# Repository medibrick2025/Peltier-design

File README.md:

# Peltier Brick Controller

## Description

The Peltier Brick is a modular controller designed to operate two independent Peltier heating and cooling modules. Each channel uses an IR2113 gate driver together with IRF3205 MOSFETs to form a switching stage that allows bidirectional current flow. By reversing the current through the Peltier device, the system can provide both heating and cooling.

A microcontroller generates PWM signals to regulate the power delivered to each Peltier element and control the temperature of each channel independently.

---

## PCB Layout

The images below show the front and back sides of the PCB design.

## Schematics

The image below shows the circuit schematic for the PCB.

---

## Electrical Hardware

KiCad PCB design files and manufacturing outputs:

[Electrical Hardware](Electrical_Hardware/)

---

## GUI

The project also includes a graphical user interface (GUI) for system control and monitoring.

The GUI supports basic interaction with the Peltier system, including control input and display of system status.

[GUI](GUI/)

---

## Datasheets and Design Notes

Power driver discussion and reference documentation:

[DataSheet](DataSheet/)

---

## Assembly and instructions

These are the [Assebly and Instructions](Assembly_and_instructions/)

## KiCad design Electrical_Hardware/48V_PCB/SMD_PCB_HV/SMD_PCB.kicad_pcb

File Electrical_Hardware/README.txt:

# PCB Ordering Guide

This folder contains the PCB manufacturing files for the Peltier hardware system.  

## PCB File Locations

```text
Electrical_Hardware/12V_PCB/SMD_PCB/
Electrical_Hardware/48V_PCB/SMD_PCB_HV/
Electrical_Hardware/Faceplate_PCB/
```

## How to Order the PCB

1. Download this repository from GitHub by clicking **Code → Download ZIP**, or clone it with Git.  

2. Open the `Electrical_Hardware` folder and choose the PCB folder you want to order.  

3. Compress the selected PCB folder into a `.zip` file.  

```text
12V_PCB/SMD_PCB/       →  SMD_PCB.zip
48V_PCB/SMD_PCB_HV/    →  SMD_PCB_HV.zip
Faceplate_PCB/         →  Faceplate_PCB.zip
```

4. Upload the `.zip` file to PCBWay as the Gerber file package.  

5. Check the PCB preview, confirm the order settings, and submit the order.  

PCBWay will review the files before manufacturing.

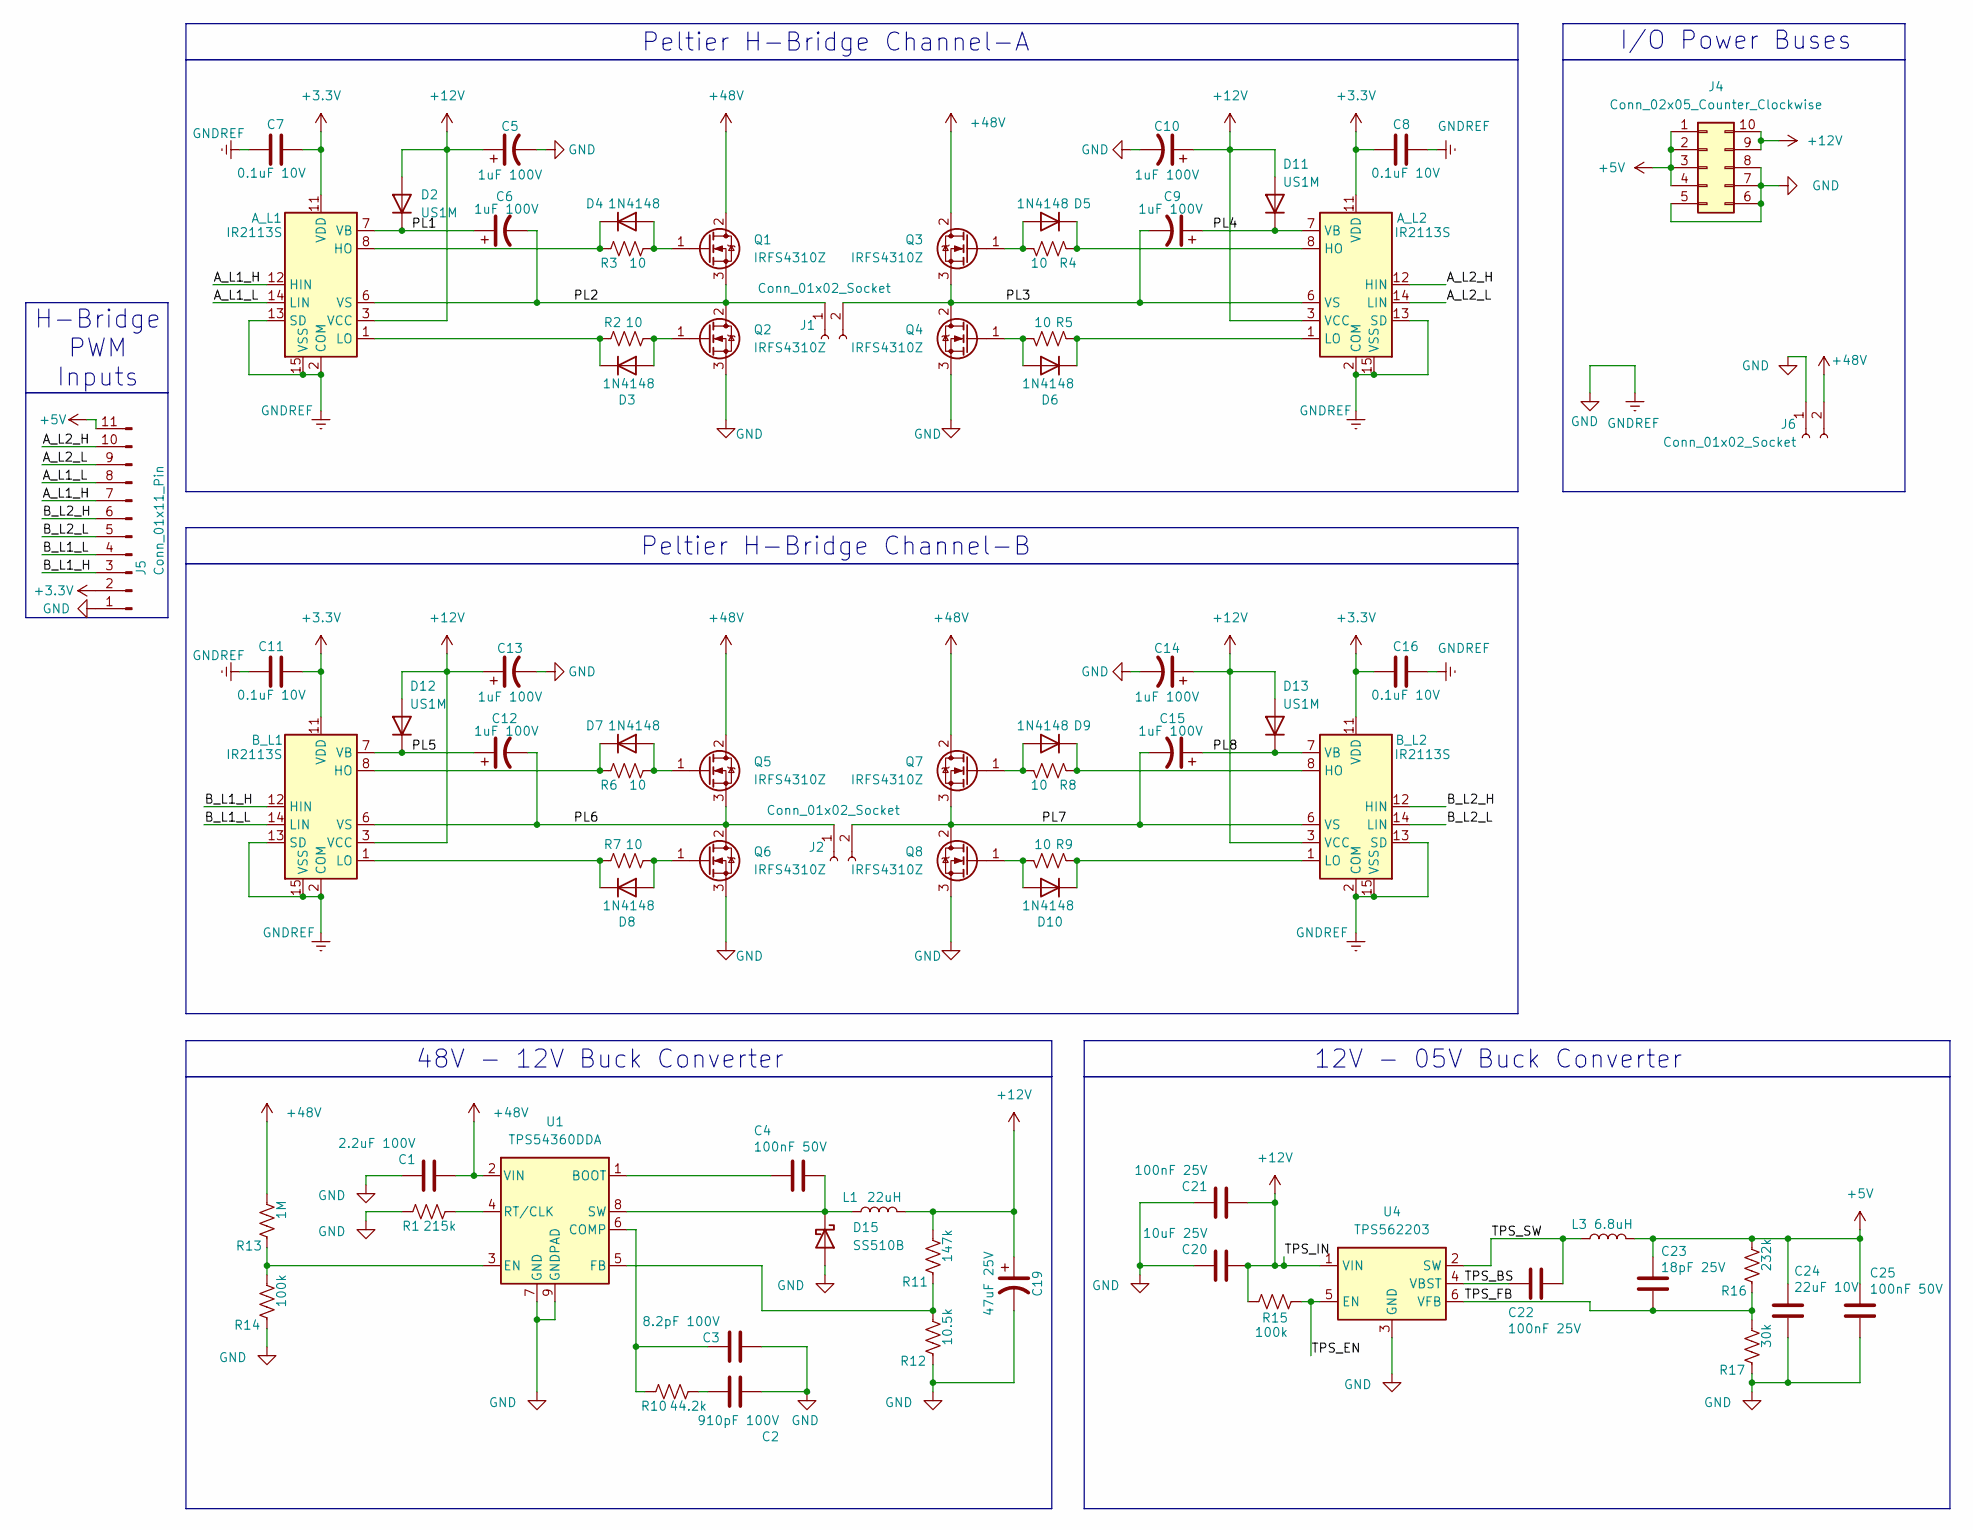
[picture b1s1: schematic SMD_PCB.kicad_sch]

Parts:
A_L1, A_L2: IR2113S; SOIC-16W_7.5x10.3mm_P1.27mm
B_L1, B_L2: IR2113S; SOIC-16W_7.5x10.3mm_P1.27mm
C1: 2.2uF 100V; C_1210_3225Metric
C2: 910pF 100V; C_0805_2012Metric
C3: 8.2pF 100V; C_0805_2012Metric
C4, C25: 100nF 50V; C_0603_1608Metric
C5, C6, C9, C10, C12, C13, C14, C15: 1uF 100V; C_1206_3216Metric
C7, C8, C11, C16: 0.1uF 10V; C_1206_3216Metric
C19: 47uF 25V; C_1206_3216Metric
C20: 10uF 25V; C_0805_2012Metric
C21, C22: 100nF 25V; C_0603_1608Metric
C23: 18pF 25V; C_0201_0603Metric
C24: 22uF 10V; C_0805_2012Metric
D2, D11, D12, D13: US1M; D_SMA
D3, D4, D5, D6, D7, D8, D9, D10: 1N4148; D_SOD-123
D15: SS510B; D_SMB
J1, J2, J6: Conn_01x02_Socket; AMASS_XT30PW-F_1x02_P2.50mm_Horizontal
J4: Conn_02x05_Counter_Clockwise; JST_PHD_B10B-PHDSS_2x05_P2.00mm_Vertical
J5: Conn_01x11_Pin; PinHeader_1x11_P2.54mm_Vertical
L1: 22uH; L_Bourns_SRR1260
L3: 6.8uH; L_Changjiang_FTC404030S
Q1, Q2, Q3, Q4, Q5, Q6, Q7, Q8: IRFS4310Z; TO-263-2
R1: 215k; R_0805_2012Metric
R2, R3, R4, R5, R6, R7, R8, R9: 10; R_1206_3216Metric
R10: 44.2k; R_0805_2012Metric
R11: 147k; R_0805_2012Metric
R12: 10.5k; R_0805_2012Metric
R13: 1M; R_0805_2012Metric
R14, R15: 100k; R_0805_2012Metric
R16: 232k; R_0805_2012Metric
R17: 30k; R_0805_2012Metric
U1: TPS54360DDA; TI_SO-PowerPAD-8_ThermalVias
U4: TPS562203; SOT-563

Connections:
+3.3V: A_L1.11 (VDD), A_L2.11 (VDD), B_L1.11 (VDD), B_L2.11 (VDD), C7.2, C8.2, C11.2, C16.2, J5.2
+5V: C23.2, C24.2, C25.2, J4.1, J4.2, J4.3, J4.4, J5.11, L3.2, R16.2
+12V: A_L1.3 (VCC), A_L2.3 (VCC), B_L1.3 (VCC), B_L2.3 (VCC), C5.1, C10.1, C13.1, C14.1, C19.1, C20.2, C21.2, D2.2 (A), D11.2 (A), D12.2 (A), D13.2 (A), J4.9, J4.10, L1.2, R11.2, R15.1, U4.1 (VIN)
+48V: C1.2, J6.2, Q1.2 (D), Q3.2 (D), Q5.2 (D), Q7.2 (D), R13.2, U1.2 (VIN)
/A_L1_H: A_L1.12 (HIN), J5.7
/A_L1_L: A_L1.14 (LIN), J5.8
/A_L2_H: A_L2.12 (HIN), J5.10
/A_L2_L: A_L2.14 (LIN), J5.9
/B_L1_H: B_L1.12 (HIN), J5.3
/B_L1_L: B_L1.14 (LIN), J5.4
/B_L2_H: B_L2.12 (HIN), J5.6
/B_L2_L: B_L2.14 (LIN), J5.5
/PL1: A_L1.7 (VB), C6.1, D2.1 (K)
/PL2: A_L1.6 (VS), C6.2, J1.1, Q1.3 (S), Q2.2 (D)
/PL3: A_L2.6 (VS), C9.2, J1.2, Q3.3 (S), Q4.2 (D)
/PL4: A_L2.7 (VB), C9.1, D11.1 (K)
/PL5: B_L1.7 (VB), C12.1, D12.1 (K)
/PL6: B_L1.6 (VS), C12.2, J2.1, Q5.3 (S), Q6.2 (D)
/PL7: B_L2.6 (VS), C15.2, J2.2, Q7.3 (S), Q8.2 (D)
/PL8: B_L2.7 (VB), C15.1, D13.1 (K)
/TPS_BS: C22.2, U4.4 (VBST)
/TPS_EN: R15.2, U4.5 (EN)
/TPS_FB: C23.1, R16.1, R17.2, U4.6 (VFB)
/TPS_SW: C22.1, L3.1, U4.2 (SW)
GND: A_L1.2 (COM), A_L1.13 (SD), A_L1.15 (VSS), A_L2.2 (COM), A_L2.13 (SD), A_L2.15 (VSS), B_L1.2 (COM), B_L1.13 (SD), B_L1.15 (VSS), B_L2.2 (COM), B_L2.13 (SD), B_L2.15 (VSS), C1.1, C2.2, C3.2, C5.2, C7.1, C8.1, C10.2, C11.1, C13.2, C14.2, C16.1, C19.2, C20.1, C21.1, C24.1, C25.1, D15.2 (A), J4.5, J4.6, J4.7, J4.8, J5.1, J6.1, Q2.3 (S), Q4.3 (S), Q6.3 (S), Q8.3 (S), R1.1, R12.1, R14.1, R17.1, U1.7 (GND), U1.9 (GNDPAD), U4.3 (GND)
unnamed: A_L1.8 (HO), D4.1 (K), R3.1
unnamed: A_L1.1 (LO), D3.1 (K), R2.1
unnamed: A_L2.8 (HO), D5.1 (K), R4.1
unnamed: A_L2.1 (LO), D6.1 (K), R5.1
unnamed: B_L1.8 (HO), D7.1 (K), R6.1
unnamed: B_L1.1 (LO), D8.1 (K), R7.1
unnamed: B_L2.8 (HO), D9.1 (K), R8.1
unnamed: B_L2.1 (LO), D10.1 (K), R9.1
unnamed: C2.1, R10.2
unnamed: D3.2 (A), Q2.1 (G), R2.2
unnamed: D4.2 (A), Q1.1 (G), R3.2
unnamed: D5.2 (A), Q3.1 (G), R4.2
unnamed: D6.2 (A), Q4.1 (G), R5.2
unnamed: D7.2 (A), Q5.1 (G), R6.2
unnamed: D8.2 (A), Q6.1 (G), R7.2
unnamed: D9.2 (A), Q7.1 (G), R8.2
unnamed: D10.2 (A), Q8.1 (G), R9.2
unnamed: C4.1, D15.1 (K), L1.1, U1.8 (SW)
unnamed: C4.2, U1.1 (BOOT)
unnamed: C3.1, R10.1, U1.6 (COMP)
unnamed: R13.1, R14.2, U1.3 (EN)
unnamed: R11.1, R12.2, U1.5 (FB)
unnamed: R1.2, U1.4 (RT/CLK)

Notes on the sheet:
I/O Power Buses
H-Bridge PWM Inputs
12V - 05V Buck Converter
Peltier H-Bridge Channel-A
Peltier H-Bridge Channel-B
48V - 12V Buck Converter

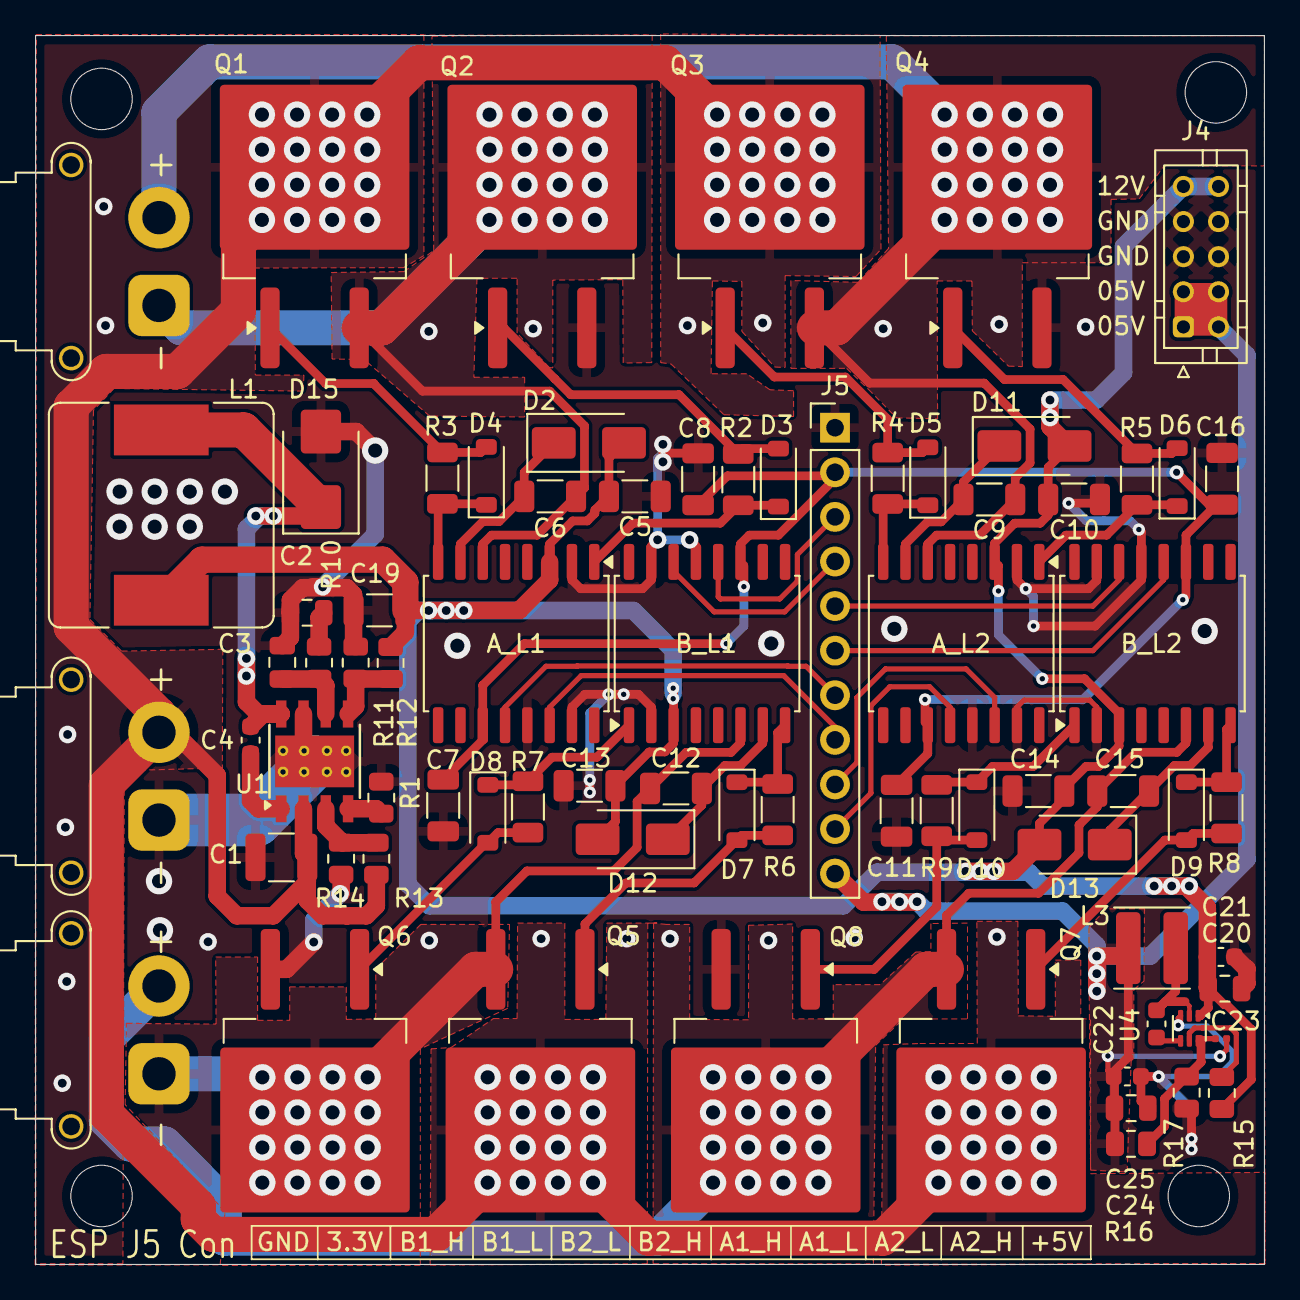
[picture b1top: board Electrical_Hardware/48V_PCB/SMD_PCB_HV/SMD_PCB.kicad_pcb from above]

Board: 2 copper layers, 70.0 x 70.0 mm, 74 parts (0 on the bottom side), 48 nets.

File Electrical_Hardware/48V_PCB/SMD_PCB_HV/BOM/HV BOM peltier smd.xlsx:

Item # | Designator | Qty | Manufacturer | Mfg Part # | LCSC Part# | Description / Value | Packaging | Type | Cost | Footprint | Remark
1 | Q1,Q2,Q3,Q4,Q5,Q6,Q7,Q8 | 8 | HXY MOSFET | IRFS4310ZTRLPBF-HXY | C20606279 | N-Channel 100V 260A 379W Surface Mount TO-263 | TO-263 | SMD |  | TO-263-3_TabPin2
2 | R9,R6,R4,R2,R5,R3,R8,R7 | 8 | YAGEO | RC1206FR-0710RL | C108080 | RES 10Ω ±1% 250mW 1206 | 1206 | SMD |  | R_1206_3216Metric
3 | B_L2,A_L2,A_L1,B_L1 | 4 | Minos | IR2113S-MNS | C47967297 | IR2113 | SOIC-16 | SMD |  | SOIC-16W_7.5x10.3mm_P1.27mm
4 | C16,C8,C11,C7 | 4 | Samsung Electro-Mechanics | CL31B104KBCNNNC | C24497 | 0.1uF 50V | 1206 | SMD |  | C_1206_3216Metric
5 | D5,D6,D10,D4,D8,D9,D3,D7 | 8 | JSMSEMI | 1N4148W | C917030 | 1N4148 | D_SOD-123 | SMD |  | D_SOD-123
6 | C14,C13,C10,C9,C12,C5,C6,C15 | 8 | YAGEO | AC1206KKX7R0BB105 | C2936627 | 1uF ±10% 100V Ceramic Capacitor X7R 1206 | 1206 | SMD |  | C_1206_3216Metric
7 | R1 | 1 | YAGEO | RT0805FRE07215KL | C706379 | RES 215kΩ ±1% 125mW 0805 | R_0805_2012Metric | SMD |  | R_0805_2012Metric
8 | R10 | 1 | YAGEO | RT0805BRD0744K2L | C865498 | RES 44.2kΩ ±0.1% 125mW 0805 | 805 | SMD |  | R_0805_2012Metric
9 | R14,R15 | 2 | YAGEO | RC0805FR-07100KL | C96346 | RES 100kΩ ±1% 125mW 0805 | 805 | SMD |  | R_0805_2012Metric
10 | R11 | 1 | YAGEO | RC0805FR-07147KL | C483012 | RES 147kΩ ±1% 125mW 0805 | 805 | SMD |  | R_0805_2012Metric
11 | R16 | 1 | FOJAN | FRC0805F2323TS | C2974036 | RES 232kΩ ±1% 125mW 0805 | 805 | SMD |  | R_0805_2012Metric
12 | R17 | 1 | YAGEO | RC0805FR-0730KL | C126352 | RES 30kΩ ±1% 125mW 0805 | 805 | SMD |  | R_0805_2012Metric
13 | R12 | 1 | UNI-ROYAL | 0805W8F1052T5E | C40086 | RES 10.5kΩ ±1% 125mW 0805 | 805 | SMD |  | R_0805_2012Metric
14 | R13 | 1 | YAGEO | RC0805FR-071ML | C107700 | RES 1MΩ ±1% 125mW 0805 | 805 | SMD |  | R_0805_2012Metric
15 | U1 | 1 | TI | TPS54360DDAR | C44377 | 60V Input, 3.5A Output Step-Down DC-DC Converter | SOIC-8-EP | SMD |  | TI_SO-PowerPAD-8_ThermalVias
16 | U4 | 1 | TI | TPS562203DRLR | C22445511 | 4.2V to 17V Input, 2A Output, Synchronous Buck Converter | SOT-563 | SMD |  | SOT-563
17 | C1 | 1 | Samsung Electro-Mechanics | CL32B225KCJSNNE | C55151 | 2.2uF ±10% 100V Ceramic Capacitor X7R 1210 | 1210 | SMD |  | C_1210_3225Metric
18 | C2 | 1 | YAGEO | AS0805KRX7R0BB472 | C1853298 | 4.7nF X7R ±10% 100V 0805 Ceramic Capacitors RoHS | 805 | SMD |  | C_0805_2012Metric
19 | C3 | 1 | MEGSINE | MCA08HQ8R2C251T7 | C42432098 | CAP CER 8.2pF 250V 0805 | 805 | SMD |  | C_0805_2012Metric
20 | C24 | 1 | YAGEO | CC0805MKX5R6BB226 | C109314 | CAP CER 22uF 10V X5R 0805 | 805 | SMD |  | C_0805_2012Metric
21 | C23 | 1 | muRata | GRM0335C1E180FA01D | C488333 | CAP CER 18pF 25V C0G 0201 | 201 | SMD |  | C_0201_0603Metric
22 | C4,C21,C22,C25 | 1 | YAGEO | CC0603KRX7R9BB104 | C14663 | CAP CER 100nF 50V X7R 0603 | 603 | SMD |  | C_0603_1608Metric
24 | C20 | 1 | CCTC | TCC0805X5R106K250FT | C5448891 | CAP CER 10uF 25V X5R 0805 | 805 | SMD |  | C_0805_2012Metric
25 | C19 | 1 | Chinocera | HGC1206R5476M250NSPJ | C22367835 | CAP CER 47uF 25V X5R 1206 | 1206 | SMD |  | C_1206_3216Metric
26 | D13,D12,D2,D11 | 4 | VISHAY | US1M-E3/61T | C81191 | Diode 1kV 1A SMA(DO-214AC) | SMA(DO-214AC) | SMD |  | D_SMA
27 | D15 | 1 | MDD(Microdiode Semiconductor) | SS510B | C65011 | DIODE SCHOTTKY 100V SMB(DO-214AA) | SMB(DO-214AA) | SMD |  | D_SMB
28 | L3 | 1 | cjiang | FTC404030S6R8MBCA | C39676084 | FIXED IND 6.8uH 4.2A 62mΩ SMD,4.1x4.1mm | SMD,4.1x4.1mm | SMD |  | L_Changjiang_FTC404030S
29 | L1 | 1 | BOURNS | SRR1260-220M | C3224283 | 4A 22uH 43mΩ 3.7A ±20% SMD,12.5x12.5mm Fixed Inductors RoHS | SMD,12.5x12.5mm | SMD |  | L_Bourns_SRR1260
30 | J4 | 1 | JST | B10B-PHDSS-B(LF)(SN) | C158039 |  |  |  |  | JST_PHD_B10B-PHDSS_2x05_P2.00mm_Vertical
31 | J1,J2,J6 | 3 | Changzhou Amass Elec | XT30PW-M30.G.Y | C431092 | Banana and Tip Connector Adapters RoHS | - |  |  | AMASS_XT30PW-F_1x02_P2.50mm_Horizontal
32 | J5 | 1 |  |  |  |  |  |  |  | PinHeader_1x11_P2.54mm_Vertical | DNP

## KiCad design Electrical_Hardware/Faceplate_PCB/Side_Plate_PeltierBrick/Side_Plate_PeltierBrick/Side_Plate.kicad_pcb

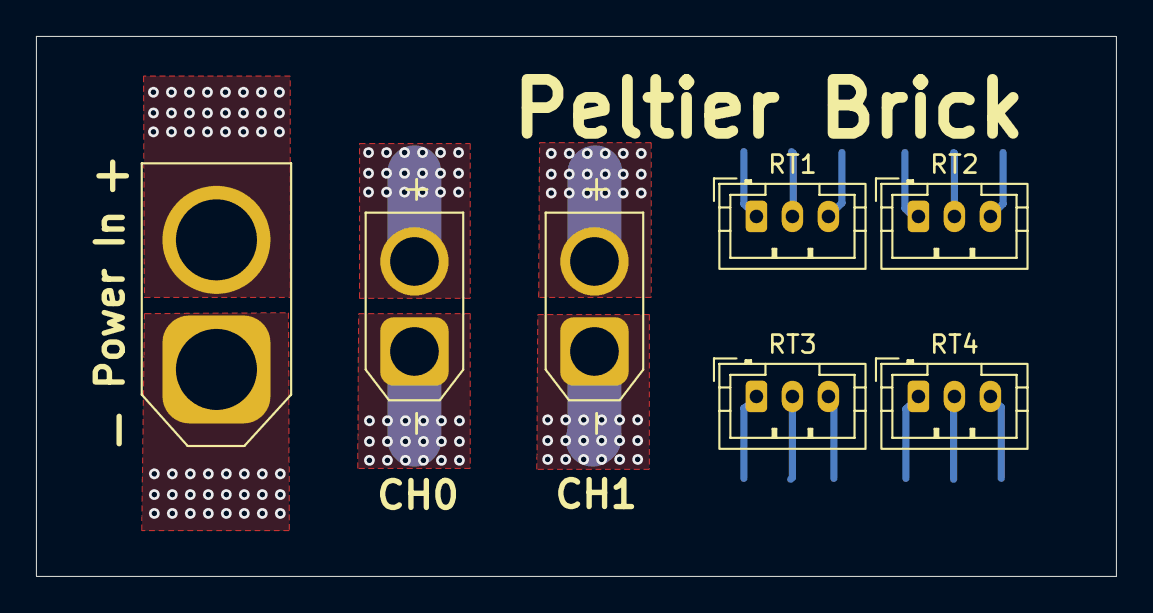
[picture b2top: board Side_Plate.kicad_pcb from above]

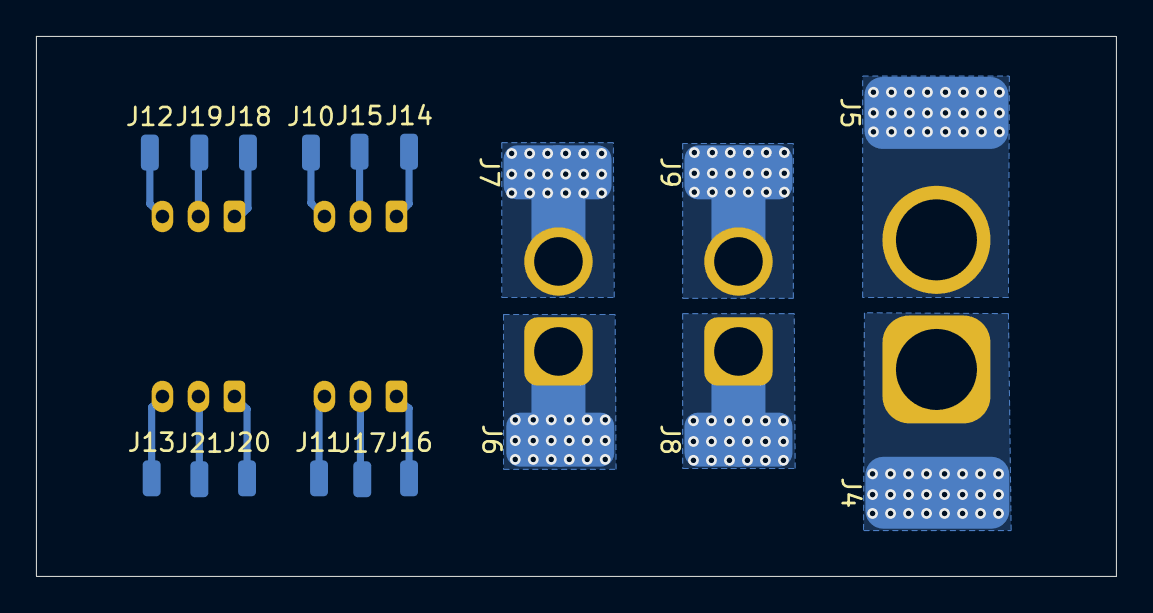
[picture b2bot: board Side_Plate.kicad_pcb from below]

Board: 2 copper layers, 60.0 x 30.0 mm, 25 parts (18 on the bottom side), 18 nets.

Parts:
J1, J3: Conn_01x02; AMASS_XT30U-M_1x02_P5.0mm_Vertical
J2: Conn_01x02; AMASS_XT60-M_1x02_P7.20mm_Vertical
J4, J5: Conn_01x01; SolderWirePad_1x01_SMD_4x8mm
J6, J7, J8, J9: Conn_01x01; SolderWirePad_1x01_SMD_3x6mm
J10, J11, J12, J13, J14, J15, J16, J17, J18, J19, J20, J21: Conn_01x01; SolderWirePad_1x01_SMD_1x2mm
RT1, RT2, RT3, RT4: Conn_01x03; JST_PH_B3B-PH-K_1x03_P2.00mm_Vertical

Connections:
/CH0_A: J1.1, J8.1
/CH0_B: J1.2, J9.1
/CH1_A: J3.1, J6.1
/CH1_B: J3.2, J7.1
/GND: J2.1, J4.1
/VBUS: J2.2, J5.1
unnamed: J10.1, RT1.3
unnamed: J11.1, RT3.3
unnamed: J12.1, RT2.3
unnamed: J13.1, RT4.3
unnamed: J14.1, RT1.1
unnamed: J15.1, RT1.2
unnamed: J16.1, RT3.1
unnamed: J17.1, RT3.2
unnamed: J18.1, RT2.1
unnamed: J19.1, RT2.2
unnamed: J20.1, RT4.1
unnamed: J21.1, RT4.2

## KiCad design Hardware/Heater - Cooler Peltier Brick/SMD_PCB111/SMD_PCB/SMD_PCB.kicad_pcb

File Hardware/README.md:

# Hardware

This directory contains the **PCB hardware design files** for the Peltier controller.

---

## PCB Layout

| Front | Back |
|------|------|
|  |  |

## Schematics

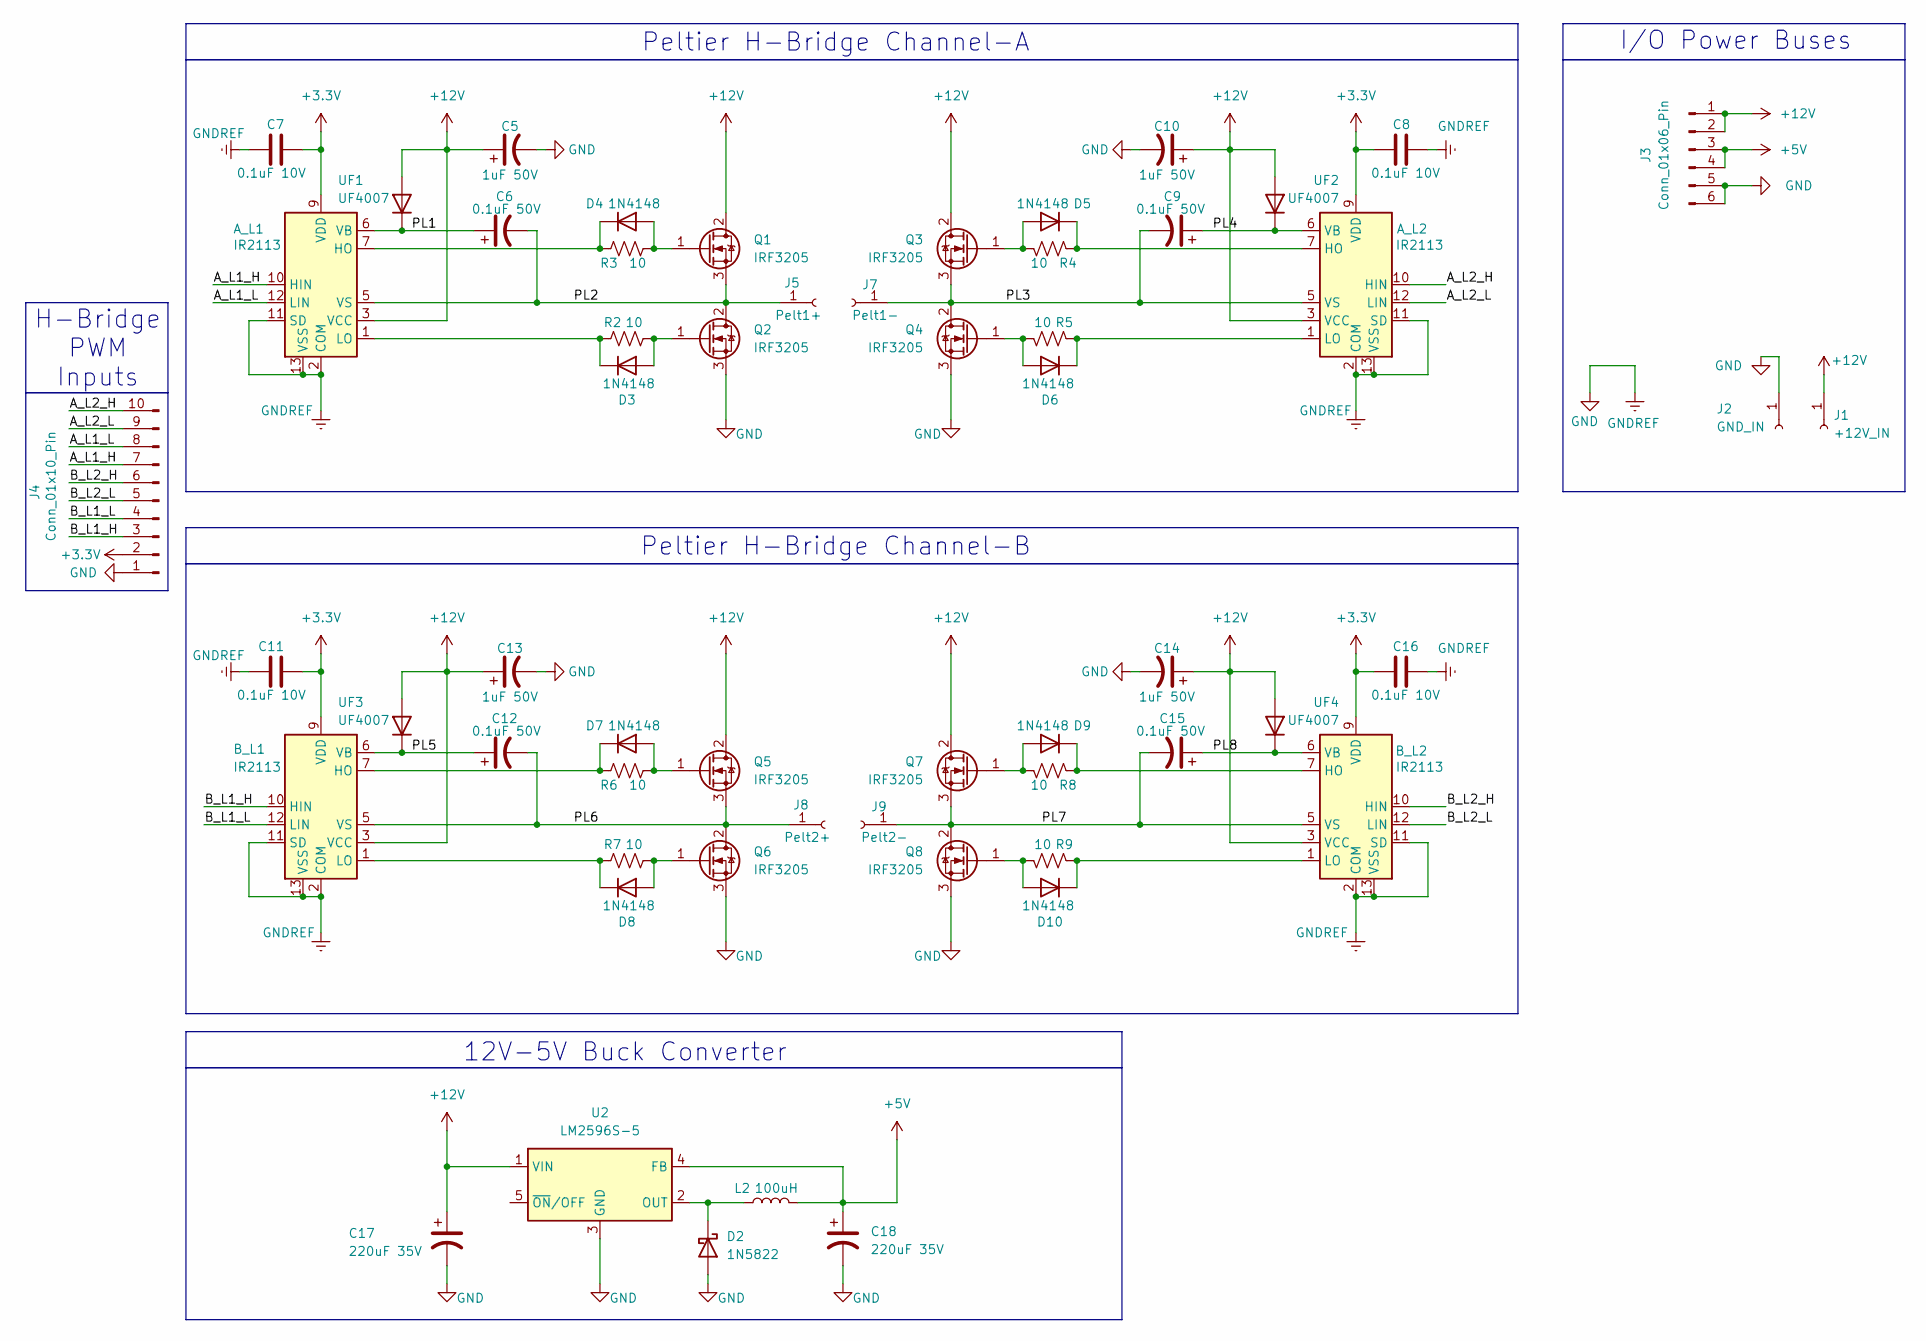
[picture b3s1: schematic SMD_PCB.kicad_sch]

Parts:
A_L1, A_L2: IR2113; SOIC-16W_7.5x10.3mm_P1.27mm
B_L1, B_L2: IR2113; SOIC-16W_7.5x10.3mm_P1.27mm
C5, C10, C13, C14: 1uF 50V; C_1206_3216Metric
C6, C9, C12, C15: 0.1uF 50V; C_1206_3216Metric
C7, C8, C11, C16: 0.1uF 10V; C_1206_3216Metric
C17, C18: 220uF 35V; CP_Elec_8x10
D2: 1N5822; D_SMC
D3, D4, D5, D6, D7, D8, D9, D10: 1N4148; D_SOD-123
J1: +12V_IN; SolderWire-1sqmm_1x01_D1.4mm_OD3.9mm
J2: GND_IN; SolderWire-1sqmm_1x01_D1.4mm_OD3.9mm
J3: Conn_01x06_Pin; PinHeader_1x06_P2.54mm_Vertical
J4: Conn_01x10_Pin; PinHeader_1x10_P2.54mm_Vertical
J5: Pelt1+; SolderWire-1sqmm_1x01_D1.4mm_OD3.9mm
J7: Pelt1-; SolderWire-1sqmm_1x01_D1.4mm_OD3.9mm
J8: Pelt2+; SolderWire-1sqmm_1x01_D1.4mm_OD3.9mm
J9: Pelt2-; SolderWire-1sqmm_1x01_D1.4mm_OD3.9mm
L2: 100uH; L_TDK_SLF12575
Q1, Q2, Q3, Q4, Q5, Q6, Q7, Q8: IRF3205; TO-263-3_TabPin2
R2, R3, R4, R5, R6, R7, R8, R9: 10; R_1206_3216Metric
U2: LM2596S-5; TO-263-5_TabPin3
UF1, UF2, UF3, UF4: UF4007; D_SMA

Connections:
+3.3V: A_L1.9 (VDD), A_L2.9 (VDD), B_L1.9 (VDD), B_L2.9 (VDD), C7.2, C8.2, C11.2, C16.2, J4.2
+5V: C18.1, J3.3, J3.4, L2.2, U2.4 (FB)
+12V: A_L1.3 (VCC), A_L2.3 (VCC), B_L1.3 (VCC), B_L2.3 (VCC), C5.1, C10.1, C13.1, C14.1, C17.1, J1.1, J3.1, J3.2, Q1.2 (D), Q3.2 (D), Q5.2 (D), Q7.2 (D), U2.1 (VIN), UF1.2 (A), UF2.2 (A), UF3.2 (A), UF4.2 (A)
/A_L1_H: A_L1.10 (HIN), J4.7
/A_L1_L: A_L1.12 (LIN), J4.8
/A_L2_H: A_L2.10 (HIN), J4.10
/A_L2_L: A_L2.12 (LIN), J4.9
/B_L1_H: B_L1.10 (HIN), J4.3
/B_L1_L: B_L1.12 (LIN), J4.4
/B_L2_H: B_L2.10 (HIN), J4.6
/B_L2_L: B_L2.12 (LIN), J4.5
/PL1: A_L1.6 (VB), C6.1, UF1.1 (K)
/PL2: A_L1.5 (VS), C6.2, J5.1, Q1.3 (S), Q2.2 (D)
/PL3: A_L2.5 (VS), C9.2, J7.1, Q3.3 (S), Q4.2 (D)
/PL4: A_L2.6 (VB), C9.1, UF2.1 (K)
/PL5: B_L1.6 (VB), C12.1, UF3.1 (K)
/PL6: B_L1.5 (VS), C12.2, J8.1, Q5.3 (S), Q6.2 (D)
/PL7: B_L2.5 (VS), C15.2, J9.1, Q7.3 (S), Q8.2 (D)
/PL8: B_L2.6 (VB), C15.1, UF4.1 (K)
GND: A_L1.2 (COM), A_L1.11 (SD), A_L1.13 (VSS), A_L2.2 (COM), A_L2.11 (SD), A_L2.13 (VSS), B_L1.2 (COM), B_L1.11 (SD), B_L1.13 (VSS), B_L2.2 (COM), B_L2.11 (SD), B_L2.13 (VSS), C5.2, C7.1, C8.1, C10.2, C11.1, C13.2, C14.2, C16.1, C17.2, C18.2, D2.2 (A), J2.1, J3.5, J3.6, J4.1, Q2.3 (S), Q4.3 (S), Q6.3 (S), Q8.3 (S), U2.3 (GND)
unnamed: A_L1.7 (HO), D4.1 (K), R3.1
unnamed: A_L1.1 (LO), D3.1 (K), R2.1
unnamed: A_L2.7 (HO), D5.1 (K), R4.1
unnamed: A_L2.1 (LO), D6.1 (K), R5.1
unnamed: B_L1.7 (HO), D7.1 (K), R6.1
unnamed: B_L1.1 (LO), D8.1 (K), R7.1
unnamed: B_L2.7 (HO), D9.1 (K), R8.1
unnamed: B_L2.1 (LO), D10.1 (K), R9.1
unnamed: D2.1 (K), L2.1, U2.2 (OUT)
unnamed: D3.2 (A), Q2.1 (G), R2.2
unnamed: D4.2 (A), Q1.1 (G), R3.2
unnamed: D5.2 (A), Q3.1 (G), R4.2
unnamed: D6.2 (A), Q4.1 (G), R5.2
unnamed: D7.2 (A), Q5.1 (G), R6.2
unnamed: D8.2 (A), Q6.1 (G), R7.2
unnamed: D9.2 (A), Q7.1 (G), R8.2
unnamed: D10.2 (A), Q8.1 (G), R9.2

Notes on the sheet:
I/O Power Buses
H-Bridge PWM Inputs
Peltier H-Bridge Channel-A
12V-5V Buck Converter
Peltier H-Bridge Channel-B

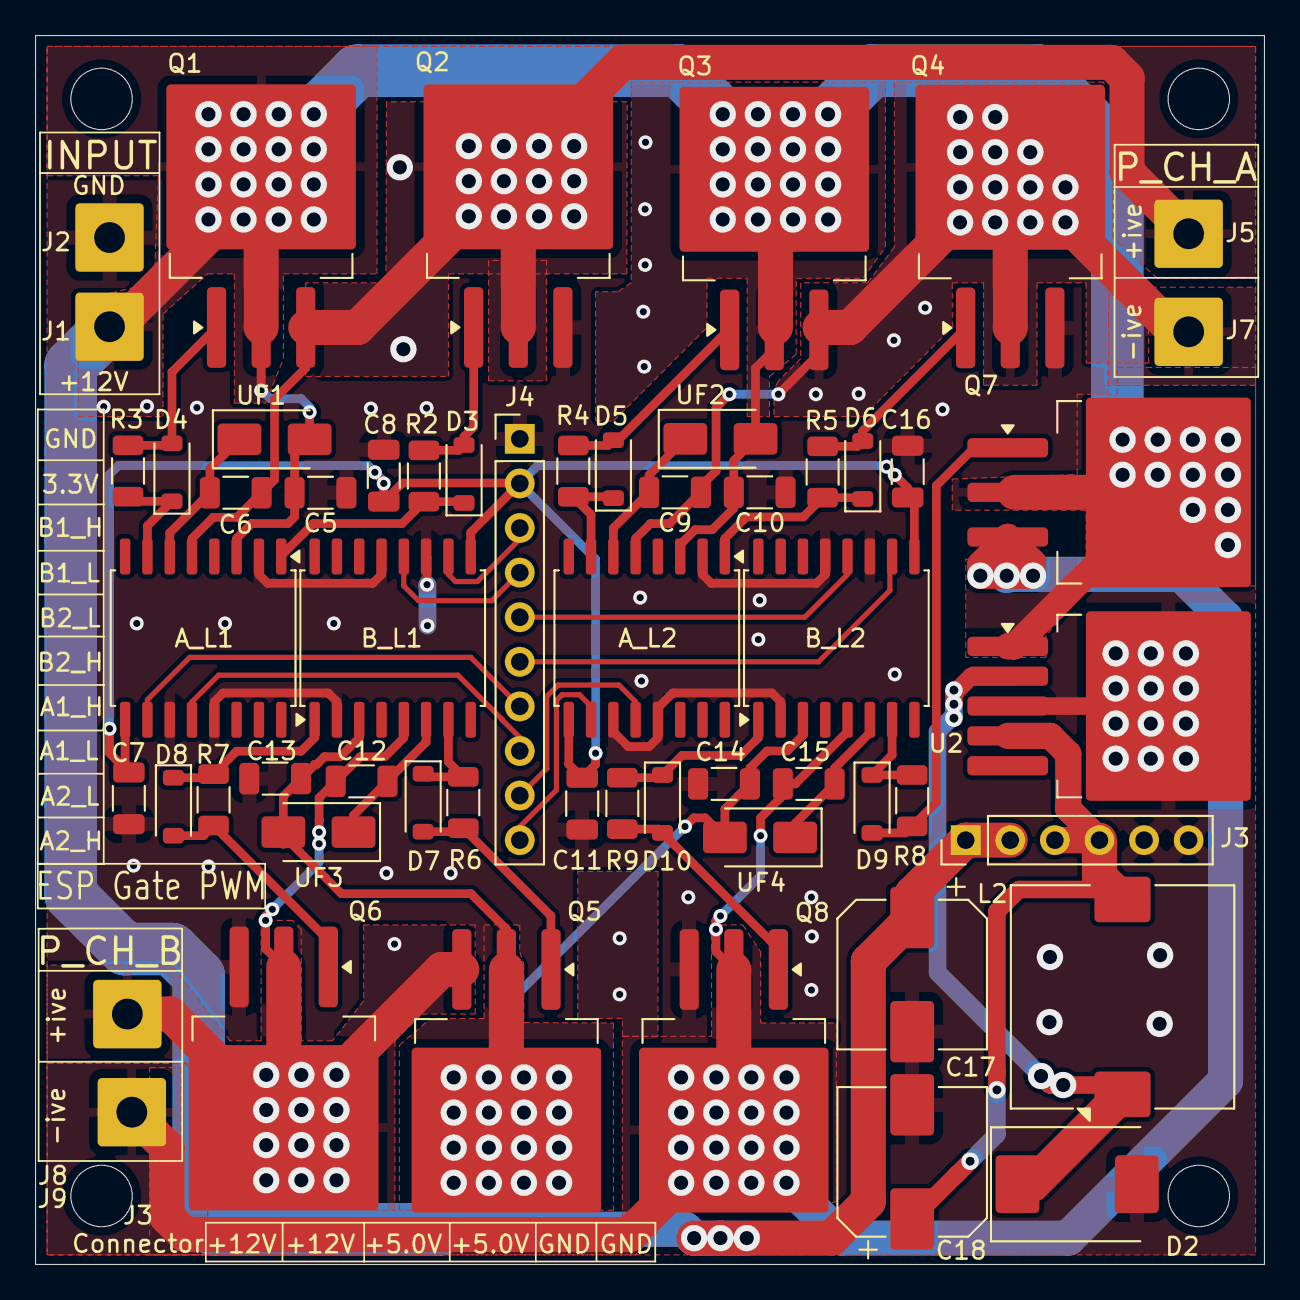
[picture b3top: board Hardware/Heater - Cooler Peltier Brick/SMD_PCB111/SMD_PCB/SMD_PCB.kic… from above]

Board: 2 copper layers, 70.0 x 70.0 mm, 57 parts (0 on the bottom side), 37 nets.

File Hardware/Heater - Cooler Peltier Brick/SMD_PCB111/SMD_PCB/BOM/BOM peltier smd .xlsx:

Item # | Designator | Qty | Manufacturer | Mfg Part # | LCSC Part# | U.S. Distributor | Description / Value | Packaging | Type | Cost | Footprint | Remark
1 | Q4,Q1,Q8,Q7,Q2,Q5,Q6,Q3 | 8 | JSMSEMI | IRF3205S-JSM | C2874633 |  | IRF3205 55V 110A 200W Surface Mount TO-263 | TO-263 | SMD |  | TO-263-3_TabPin2
2 | R9,R6,R4,R2,R5,R3,R8,R7 | 8 | YAGEO | RC1206FR-0710RL | C108080 |  | RES 10Ω ±1% 250mW 1206 | 1206 | SMD |  | R_1206_3216Metric
3 | D2 | 1 | onsemi | SS34 | C154551 |  | Diode 40V 3A SMC(DO-214AB) | SMC(DO-214AB) | SMD |  | D_SMC
4 | UF3,UF4,UF1,UF2 | 4 | VISHAY | US1M-E3/61T | C81191 |  | Diode 1kV 1A SMA(DO-214AC) | SMA(DO-214AC) | SMD |  | D_SMA
5 | C14,C13,C10,C5 | 4 | Samsung Electro-Mechanics | CL31B105KBHNNNE | C1848 |  | CAP CER 1uF 50V X7R 1206 | 1206 | SMD |  | C_1206_3216Metric
6 | B_L1,B_L2,A_L2,A_L1 | 4 | Minos | IR2113S-MNS | C47967297 |  | IR2113 | SOIC-16 | SMD |  | SOIC-16W_7.5x10.3mm_P1.27mm
7 | C18,C17 | 2 | JIERR | CS35V220M8X10 | C48935393 |  | CAP ALUM 220uF ±20% 35V SMD | 8x10 | SMD |  | CP_Elec_8x10
8 | C16,C8,C11,C7 | 4 | Samsung Electro-Mechanics | CL31B104KBCNNNC | C24497 |  | 0.1uF 50V | 1206 | SMD |  | C_1206_3216Metric
9 | D5,D6,D10,D4,D8,D9,D3,D7 | 8 | JSMSEMI | 1N4148W | C917030 |  | 1N4148 | D_SOD-123 | SMD |  | D_SOD-123
10 | C9,C12,C6,C15 | 4 | Samsung Electro-Mechanics | CL31B104KBCNNNC | C24497 |  | 0.1uF 50V | 1206 | SMD |  | C_1206_3216Metric
11 | L2 | 1 | TDK | SLF12575T-101M1R9-PF | C81470 |  | 100uH |  | SMD |  | L_TDK_SLF12575
12 | U2 | 1 | TI | LM2596S-5.0/NOPB | C116713 |  | LM2596 150-kHz 3-A Step-Down Voltage Regulator | TO-263-5 | SMD |  | TO-263-5_TabPin3
13 | J1 | 1 |  |  |  |  | +12V_IN |  | SMD |  | SolderWire-1sqmm_1x01_D1.4mm_OD3.9mm | DNP
14 | J2 | 1 |  |  |  |  | GND_IN |  | SMD |  | SolderWire-1sqmm_1x01_D1.4mm_OD3.9mm | DNP
15 | J3 | 1 |  |  |  |  | Conn_01x06_Pin |  | SMD |  | PinHeader_1x06_P2.54mm_Vertical | DNP
16 | J4 | 1 |  |  |  |  | Conn_01x10_Pin |  | SMD |  | PinHeader_1x10_P2.54mm_Vertical | DNP
17 | J5 | 1 |  |  |  |  | Pelt1+ |  | SMD |  | SolderWire-1sqmm_1x01_D1.4mm_OD3.9mm | DNP
18 | J7 | 1 |  |  |  |  | Pelt1- |  | SMD |  | SolderWire-1sqmm_1x01_D1.4mm_OD3.9mm | DNP
19 | J8 | 1 |  |  |  |  | Pelt2+ |  | SMD |  | SolderWire-1sqmm_1x01_D1.4mm_OD3.9mm | DNP
20 | J9 | 1 |  |  |  |  | Pelt2- |  | SMD |  | SolderWire-1sqmm_1x01_D1.4mm_OD3.9mm | DNP

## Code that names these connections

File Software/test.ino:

#include "driver/mcpwm_prelude.h"

#define RXD2 38
#define TXD2 39


// Channel/Bridge A
#define A_L1_H 11 
#define A_L1_L 12
#define A_L2_H 18
#define A_L2_L 13

// Channel/Bridge B
#define B_L1_H 5
#define B_L1_L 6
#define B_L2_H 10
#define B_L2_L 9

mcpwm_timer_handle_t timerA = NULL, timerB = NULL;
mcpwm_oper_handle_t oper1A = NULL, oper2A = NULL, oper1B = NULL, oper2B = NULL;
mcpwm_cmpr_handle_t cmpr1A = NULL, cmpr2A = NULL, cmpr1B = NULL, cmpr2B = NULL;
mcpwm_gen_handle_t g1AH, g1AL, g2AH, g2AL, g1BH, g1BL, g2BH, g2BL;

const uint32_t period = 250; 

void setup() {
    Serial.begin(115200);
    Serial2.begin(115200, SERIAL_8N1, RXD2, TXD2); 

    // Timer Setup
    mcpwm_timer_config_t timer_conf = {
        .clk_src = MCPWM_TIMER_CLK_SRC_DEFAULT,
        .resolution_hz = 1000000, 
        .count_mode = MCPWM_TIMER_COUNT_MODE_UP,
        .period_ticks = period, 
    };
    
    timer_conf.group_id = 0; mcpwm_new_timer(&timer_conf, &timerA);
    timer_conf.group_id = 1; mcpwm_new_timer(&timer_conf, &timerB);

    mcpwm_comparator_config_t cmpr_conf = {.flags = {.update_cmp_on_tez = true}};
    mcpwm_generator_config_t gen_conf = {};

    // --- H-BRIDGE A ---
    mcpwm_operator_config_t oper_confA = {.group_id = 0};
    mcpwm_new_operator(&oper_confA, &oper1A);
    mcpwm_new_operator(&oper_confA, &oper2A);
    mcpwm_operator_connect_timer(oper1A, timerA);
    mcpwm_operator_connect_timer(oper2A, timerA);
    
    mcpwm_new_comparator(oper1A, &cmpr_conf, &cmpr1A);
    mcpwm_new_comparator(oper2A, &cmpr_conf, &cmpr2A);

    gen_conf.gen_gpio_num = A_L1_H; mcpwm_new_generator(oper1A, &gen_conf, &g1AH);
    gen_conf.gen_gpio_num = A_L1_L; mcpwm_new_generator(oper1A, &gen_conf, &g1AL);
    gen_conf.gen_gpio_num = A_L2_H; mcpwm_new_generator(oper2A, &gen_conf, &g2AH);
    gen_conf.gen_gpio_num = A_L2_L; mcpwm_new_generator(oper2A, &gen_conf, &g2AL);

    // --- H-BRIDGE B  ---
    mcpwm_operator_config_t oper_confB = {.group_id = 1};
    mcpwm_new_operator(&oper_confB, &oper1B);
    mcpwm_new_operator(&oper_confB, &oper2B);
    mcpwm_operator_connect_timer(oper1B, timerB);
    mcpwm_operator_connect_timer(oper2B, timerB);

    mcpwm_new_comparator(oper1B, &cmpr_conf, &cmpr1B);
    mcpwm_new_comparator(oper2B, &cmpr_conf, &cmpr2B);

    gen_conf.gen_gpio_num = B_L1_H; mcpwm_new_generator(oper1B, &gen_conf, &g1BH);
    gen_conf.gen_gpio_num = B_L1_L; mcpwm_new_generator(oper1B, &gen_conf, &g1BL);
    gen_conf.gen_gpio_num = B_L2_H; mcpwm_new_generator(oper2B, &gen_conf, &g2BH);
    gen_conf.gen_gpio_num = B_L2_L; mcpwm_new_generator(oper2B, &gen_conf, &g2BL);

    // Generate PWM
    mcpwm_generator_set_action_on_timer_event(g1AH, MCPWM_GEN_TIMER_EVENT_ACTION(MCPWM_TIMER_DIRECTION_UP, MCPWM_TIMER_EVENT_EMPTY, MCPWM_GEN_ACTION_HIGH));
    mcpwm_generator_set_action_on_compare_event(g1AH, MCPWM_GEN_COMPARE_EVENT_ACTION(MCPWM_TIMER_DIRECTION_UP, cmpr1A, MCPWM_GEN_ACTION_LOW));
    mcpwm_generator_set_action_on_timer_event(g2AH, MCPWM_GEN_TIMER_EVENT_ACTION(MCPWM_TIMER_DIRECTION_UP, MCPWM_TIMER_EVENT_EMPTY, MCPWM_GEN_ACTION_HIGH));
    mcpwm_generator_set_action_on_compare_event(g2AH, MCPWM_GEN_COMPARE_EVENT_ACTION(MCPWM_TIMER_DIRECTION_UP, cmpr2A, MCPWM_GEN_ACTION_LOW));

    mcpwm_generator_set_action_on_timer_event(g1BH, MCPWM_GEN_TIMER_EVENT_ACTION(MCPWM_TIMER_DIRECTION_UP, MCPWM_TIMER_EVENT_EMPTY, MCPWM_GEN_ACTION_HIGH));
    mcpwm_generator_set_action_on_compare_event(g1BH, MCPWM_GEN_COMPARE_EVENT_ACTION(MCPWM_TIMER_DIRECTION_UP, cmpr1B, MCPWM_GEN_ACTION_LOW));
    mcpwm_generator_set_action_on_timer_event(g2BH, MCPWM_GEN_TIMER_EVENT_ACTION(MCPWM_TIMER_DIRECTION_UP, MCPWM_TIMER_EVENT_EMPTY, MCPWM_GEN_ACTION_HIGH));
    mcpwm_generator_set_action_on_compare_event(g2BH, MCPWM_GEN_COMPARE_EVENT_ACTION(MCPWM_TIMER_DIRECTION_UP, cmpr2B, MCPWM_GEN_ACTION_LOW));

    mcpwm_timer_enable(timerA);
    mcpwm_timer_start_stop(timerA, MCPWM_TIMER_START_NO_STOP);
    mcpwm_timer_enable(timerB);
    mcpwm_timer_start_stop(timerB, MCPWM_TIMER_START_NO_STOP);

    peltierA_OFF();
    peltierB_OFF();

    //peltierB_Cool(90); // TEST RUN JD
}
void peltierA_OFF() {
    mcpwm_generator_set_force_level(g1AH, 0, true); mcpwm_generator_set_force_level(g1AL, 0, true);
    mcpwm_generator_set_force_level(g2AH, 0, true); mcpwm_generator_set_force_level(g2AL, 0, true);
}

void peltierA_Cool(int duty) {
    peltierA_OFF();
    mcpwm_comparator_set_compare_value(cmpr1A, (duty * period) / 100);
    mcpwm_generator_set_force_level(g1AH, -1, true); 
    mcpwm_generator_set_force_level(g2AL, 1, true);  
}

void peltierA_Heat(int duty) {
    peltierA_OFF();
    mcpwm_comparator_set_compare_value(cmpr2A, (duty * period) / 100);
    mcpwm_generator_set_force_level(g2AH, -1, true); 
    mcpwm_generator_set_force_level(g1AL, 1, true);  
}

void peltierB_OFF() {
    mcpwm_generator_set_force_level(g1BH, 0, true); mcpwm_generator_set_force_level(g1BL, 0, true);
    mcpwm_generator_set_force_level(g2BH, 0, true); mcpwm_generator_set_force_level(g2BL, 0, true);
}

void peltierB_Cool(int duty) {
    peltierB_OFF();
    mcpwm_comparator_set_compare_value(cmpr1B, (duty * period) / 100);
    mcpwm_generator_set_force_level(g1BH, -1, true); 
    mcpwm_generator_set_force_level(g2BL, 1, true);  
}

void peltierB_Heat(int duty) {
    peltierB_OFF();
    mcpwm_comparator_set_compare_value(cmpr2B, (duty * period) / 100);
    mcpwm_generator_set_force_level(g2BH, -1, true); 
    mcpwm_generator_set_force_level(g1BL, 1, true);  
}

void loop() {

     //peltierA_OFF(); //peltierB_OFF();
    // peltierA_Cool(90);
     //peltierA_Heat(90);
     peltierB_Cool(90);
     delay(60000);
}

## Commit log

2026-03-07 Uploaded some basic documentation files and PCB design.
2026-03-07 fix md doc
2026-03-07 fix Md doc problem
2026-03-07 fix Picture problem
2026-04-04 Add GUI module, update PCB design, and improve README documentation
2026-05-06 renew the PCB_floder, uploaded the Assembly Instruction and users manul
2026-05-06 fix spelling error
2026-05-07 fix md
2026-05-07 fix GUI setup step3 problem
